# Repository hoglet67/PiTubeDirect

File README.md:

# PiTubeDirect
PiTubeDirect is a low cost Second Processor project for Acorn's 8-bit machines (Beeb, Master, Electron, Atom)
which uses two cheap chips to interface a Raspberry Pi to the Tube connector.

The Pi emulates one of a number of CPUs, and also the Tube interface chip.

A Pi Zero can emulate a 6502 Second Processor running at 274MHz.

For more information, see the project [Wiki](../../wiki).

Here's the minimal configuration, using a Pi Zero and a DIY two-chip level shifter: 

Benchmark results for the 65C02 Second Processor:

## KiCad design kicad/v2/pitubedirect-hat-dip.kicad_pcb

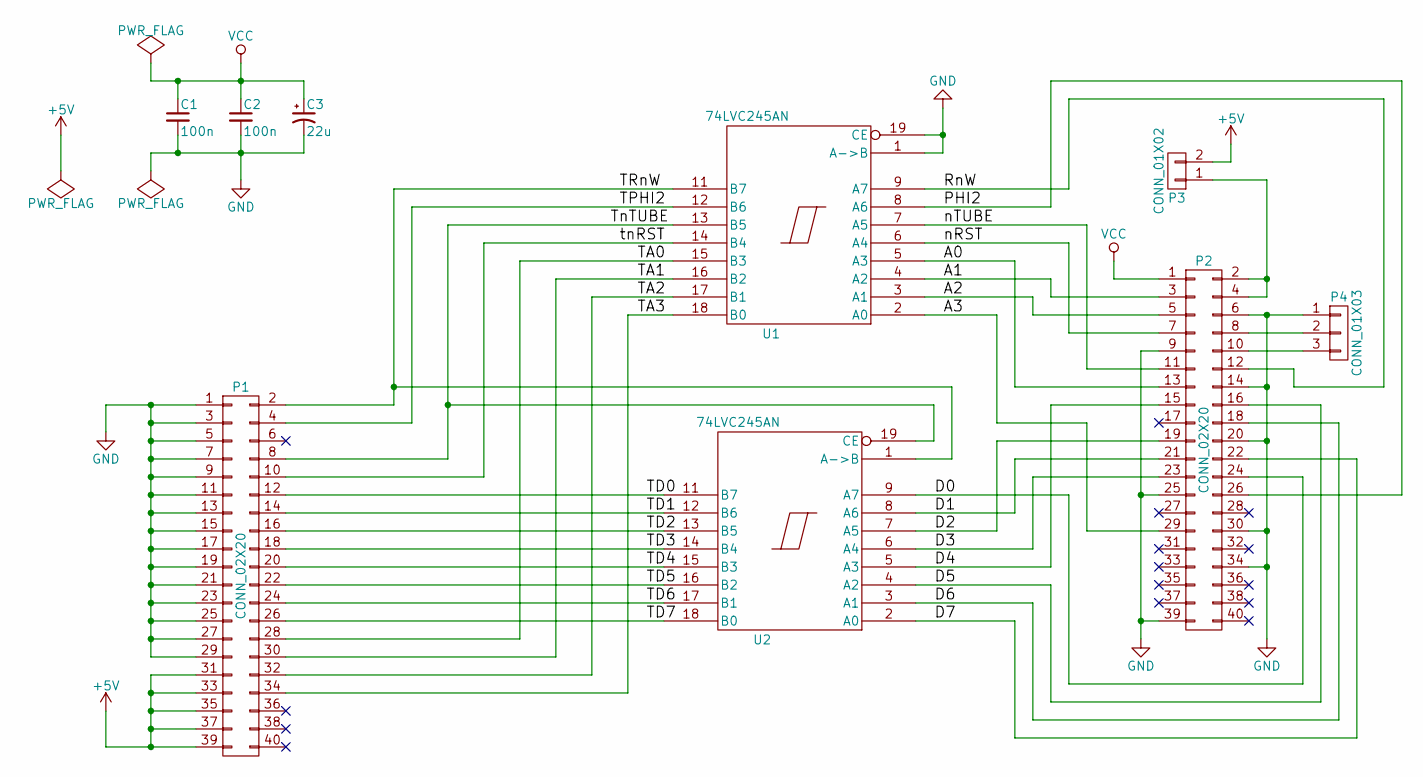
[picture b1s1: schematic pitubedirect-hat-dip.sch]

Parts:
C1, C2: 100n; C_Rect_L7_W2_P5
C3: 22u; C1V8
P1: CONN_02X20; Pin_Header_Straight_2x20
P2: CONN_02X20; Socket_Strip_Straight_2x20
P3: CONN_01X02; Pin_Header_Straight_1x02
P4: CONN_01X03; Pin_Header_Straight_1x03
U1, U2: 74LVC245AN; DIP-20_W7.62mm

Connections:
+5V: P1.31, P1.33, P1.35, P1.37, P1.39, P3.2
/A0: P2.13, U1.5 (A3)
/A1: P2.3, U1.4 (A2)
/A2: P2.5, U1.3 (A1)
/A3: P2.29, U1.2 (A0)
/D0: P2.24, U2.9 (A7)
/D1: P2.21, U2.8 (A6)
/D2: P2.19, U2.7 (A5)
/D3: P2.23, U2.6 (A4)
/D4: P2.15, U2.5 (A3)
/D5: P2.16, U2.4 (A2)
/D6: P2.18, U2.3 (A1)
/D7: P2.22, U2.2 (A0)
/PHI2: P2.26, U1.8 (A6)
/RnW: P2.12, U1.9 (A7)
/TA0: P1.28, U1.15 (B3)
/TA1: P1.30, U1.16 (B2)
/TA2: P1.32, U1.17 (B1)
/TA3: P1.34, U1.18 (B0)
/TD0: P1.12, U2.11 (B7)
/TD1: P1.14, U2.12 (B6)
/TD2: P1.16, U2.13 (B5)
/TD3: P1.18, U2.14 (B4)
/TD4: P1.20, U2.15 (B3)
/TD5: P1.22, U2.16 (B2)
/TD6: P1.24, U2.17 (B1)
/TD7: P1.26, U2.18 (B0)
/TPHI2: P1.4, U1.12 (B6)
/TRnW: P1.2, U1.11 (B7), U2.1 (A->B)
/TnTUBE: P1.8, U1.13 (B5), U2.19 (CE)
/nRST: P2.7, U1.6 (A4)
/nTUBE: P2.11, U1.7 (A5)
/tnRST: P1.10, U1.14 (B4)
GND: C1.2, C2.2, C3.2, P1.1, P1.3, P1.5, P1.7, P1.9, P1.11, P1.13, P1.15, P1.17, P1.19, P1.21, P1.23, P1.25, P1.27, P1.29, P2.6, P2.9, P2.14, P2.20, P2.25, P2.30, P2.34, P2.39, P4.1, U1.1 (A->B), U1.10 (GND), U1.19 (CE), U2.10 (GND)
unnamed: P2.2, P2.4, P3.1
unnamed: P2.8, P4.2
unnamed: P2.10, P4.3
VCC: C1.1, C2.1, C3.1, P2.1, U1.20 (VCC), U2.20 (VCC)

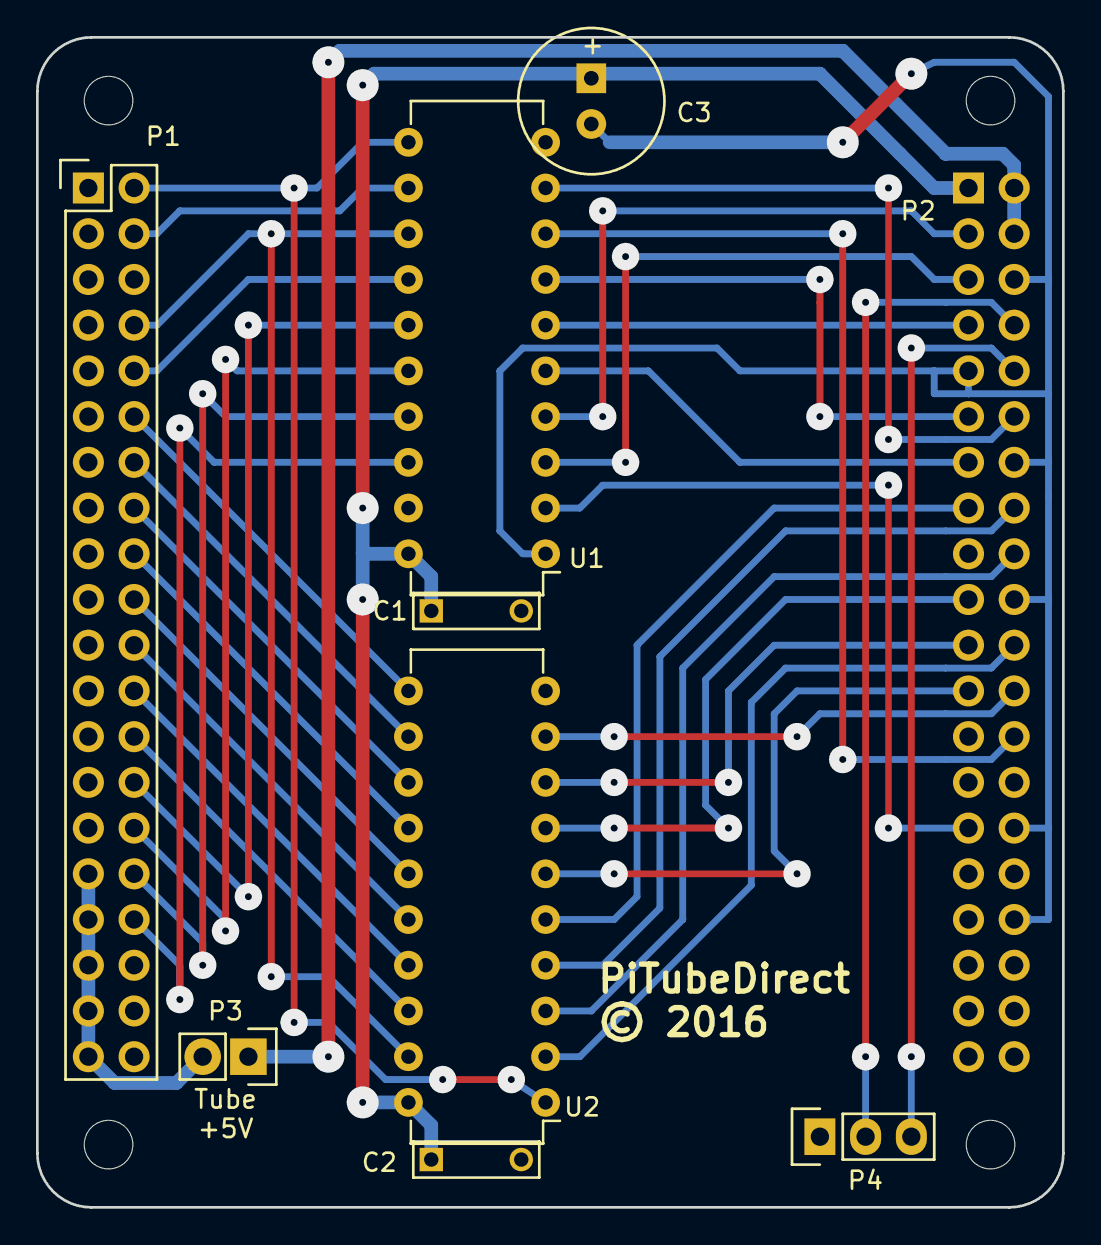
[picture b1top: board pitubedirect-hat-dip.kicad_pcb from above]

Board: 2 copper layers, 57.0 x 65.0 mm, 9 parts (0 on the bottom side), 38 nets.

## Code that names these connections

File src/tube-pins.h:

#include "rpi-base-asm.h"

#define ASS_GPFSEL0 (PERIPHERAL_BASE + 0x200000)  // controls GPIOs 0..9
#define ASS_GPFSEL1 (PERIPHERAL_BASE + 0x200004)  // controls GPIOs 10..19
#define ASS_GPFSEL2 (PERIPHERAL_BASE + 0x200008)  // controls GPIOs 20..29
#define ASS_GPSET0  (PERIPHERAL_BASE + 0x20001C)
#define ASS_GPCLR0  (PERIPHERAL_BASE + 0x200028)
#define ASS_GPLEV0  (PERIPHERAL_BASE + 0x200034)
#define ASS_GPEDS0  (PERIPHERAL_BASE + 0x200040)
#define ASS_FIQCTRL (PERIPHERAL_BASE + 0x00B20C)

//    A2 – Green  - Pin 5  – GPIO1  (GPIO3 on later models)
//    A1 – Blue   - Pin 3  – GPIO0  (GPIO2 on later models)
//    A0 – Purple – Pin 13 – GPIO21 (GPIO27 on later models)
//    D7 – Grey   - Pin 22 – GPIO25
//    D6 – White  - Pin 18 – GPIO24
//    D5 – Black  - Pin 16 – GPIO23
//    D4 – Brown  - Pin 15 – GPIO22
//    D3 – Red    - Pin 23 – GPIO11
//    D2 – Orange – Pin 19 – GPIO10
//    D1 – Yellow – Pin 21 – GPIO9
//    D0 – Green  - Pin 24 – GPIO8
//  nRST – Blue   - Pin 7  – GPIO4
// nTUBE – Purple – Pin 11 – GPIO17
//  nIRQ
//  Phi2 – Grey   - Pin 26 – GPIO7
//   RnW – White  - Pin 12 – GPIO18
//   GND – Black  - Pin 25 – GND

#define D0_BASE      (8)
#define D4_BASE      (22)

#define D7_PIN       (25)     // C2
#define D6_PIN       (24)     // C2
#define D5_PIN       (23)     // C2
#define D4_PIN       (22)     // C2
#define D3_PIN       (11)     // C1
#define D2_PIN       (10)     // C1
#define D1_PIN       (9)      // C0
#define D0_PIN       (8)      // C0

#define MAGIC_C0     ((1 << (D0_PIN * 3)) | (1 << (D1_PIN * 3)))
#define MAGIC_C1     ((1 << ((D2_PIN - 10) * 3)) | (1 << ((D3_PIN - 10) * 3)))
#define MAGIC_C2     ((1 << ((D4_PIN - 20) * 3)) | (1 << ((D5_PIN - 20) * 3)))
#define MAGIC_C3     ((1 << ((D6_PIN - 20) * 3)) | (1 << ((D7_PIN - 20) * 3)))

#define A2_PIN_40PIN       (3)
#define A1_PIN_40PIN       (2)
#define A0_PIN_40PIN       (27)

#define A2_PIN_26PIN       (1)
#define A1_PIN_26PIN       (0)
#define A0_PIN_26PIN       (21)

#define PHI2_PIN     (7)
#define NTUBE_PIN    (17)
#define NRST_PIN     (4)
#define RNW_PIN      (18)

#define D7_MASK      (1 << D7_PIN)
#define D6_MASK      (1 << D6_PIN)
#define D5_MASK      (1 << D5_PIN)
#define D4_MASK      (1 << D4_PIN)
#define D3_MASK      (1 << D3_PIN)
#define D2_MASK      (1 << D2_PIN)
#define D1_MASK      (1 << D1_PIN)
#define D0_MASK      (1 << D0_PIN)

#define PHI2_MASK    (1 << PHI2_PIN)
#define NTUBE_MASK   (1 << NTUBE_PIN)
#define NRST_MASK    (1 << NRST_PIN)
#define RNW_MASK     (1 << RNW_PIN)

#define ATTN_MASK    (1 << ATTN_PIN)
#define OVERRUN_MASK (1 << OVERRUN_PIN)
#define GLITCH_MASK  (1 << GLITCH_PIN)

#define D30_MASK     (D3_MASK | D2_MASK | D1_MASK | D0_MASK)
#define D74_MASK     (D7_MASK | D6_MASK | D5_MASK | D4_MASK)
#define D_MASK       (D74_MASK | D30_MASK)


#define TEST_PIN_26PIN     (27)
#define TEST_PIN_40PIN     (21)

#define TEST_PIN     (21)
#define TEST_MASK    (1 << TEST_PIN)
#define TEST2_PIN    (20)
#define TEST2_MASK   (1 << TEST2_PIN)
#define TEST3_PIN    (16)
#define TEST3_MASK   (1 << TEST3_PIN)

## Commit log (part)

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2022-06-02 Add consts
2022-06-03 Updated the release name to Hognose-rc5
2022-06-04 Jit make better use of strd
2022-06-05 Frame Buffer: VDU 23,0,10/11 controls cursor start/end row
2022-06-05 Jit.s : very simple optimiser to remove duplicate flag settings
    Very simple optimiser such that if the next instruction also sets the NZ flags then the current instruction doesn't need to set the flags. This can help to remove pipeline stalls especially after a l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
2022-06-05 jit.s : remove optimisation at appears to slow ARMv6 systems
2022-06-06 Frame Buffer: implement OSBYTE &A0 X=&4F/&60/&61
2022-06-06 no need to fill in last words of branches now
2022-06-06 Jit.s speed up Store ZP generation
2022-06-08 Updated the release name to Hognose-rc6
2022-06-09 PDP-11 Co Pro - fix an infinite logging loop on odd address traps
2022-06-19 Arm dissassembler : fix instructiosn of the form LDR rd,[rn,rm,LSL #xx]!
    Also remove addr_mask
2022-06-19 Arm diss : remove addr_mask
2022-06-21 arm-start.S : speed up initialisation
2022-06-25 llib6502 disassembler: significantly speed up code
    this is required so the the jitter live tracking will work on a Pizero
2022-06-25 UART : increase tx buffer size to 4Mbytes
2022-06-25 jit : large changes
    IRQ handler now local instead of using the global one
    flags used to hold of FAKE irqs till safe points in the code
    Issue #125 : memory leak removed
    various tiding
    Pizero : better instruction cache flush to improve live tracing performance also removes glitch in twinhead
    whitespace improvements
2022-06-25 Jit : remove useless ifdef
2022-07-17 ROL and ASL $80 + optimise lda #0 , JMP($0000,X)
2022-07-17 LDA $0000,Y optimise + tidy
2022-07-17 fix typo in jmp ($0000,x)
2022-07-18 faster JSR
2022-07-20 Optimise logical $0000,X or Y
2022-07-21 for dual issue remove flag setting instructions
2022-07-21 pipeline adjustment
2022-07-21 remove duplicate code
2022-07-23 CLC /SEC add to flag optimisation
2022-07-23 reorder ldy $00 ldx $00
2022-07-23 forward flags looking optimiser
2022-07-24 Add prefetch Instruction cacheline + tidy
2022-07-25 nops are faster than branches on ARMv8
2022-07-26 Tidy up registers around irqs nmis, free up R2 to be used by RTSR2
    492MHz
2022-07-29 faster sta
    528MHz. bias sta zp to non self modifying code
2022-08-16 PDP-11 Co Pro - updated client rom to 0.30 (just a version number change from 0.28e)
2022-10-07 remove cppcheck warnings
2023-01-24 Tube ULA: Added tube_debug support
2023-01-24 Tube ULA: Fix #ifdef typo
2023-01-28 gcc appears not to support eret for armv7
2023-01-28 fix cppcheck warning
2023-01-28 split out font_t and font_catalog to remove warnings
2023-01-28 Update ClockSP to ClockSP5 ( 5.08)
2023-01-28 remove warnings and simplify code
2023-01-28 Tidy
2023-01-28 Cppcheck script
2023-01-29 Add const keyword
2023-01-29 Fix binutiles 2.39 linker warning and simplify
2023-01-29 shrink pandora rom ( truncate x00)
2023-01-31 Remove unnecessary init_info() function as we nolonger take over the main VPU
2023-02-03 reduce cpu time copying strings around and reallocing ram
2023-02-04 use calloc
2023-02-05 Move IRQ handler out of AUX UART code
2023-02-05 use strcasestr
2023-03-18 Updated the release name to Hognose-fixes
2023-04-28 Add a pullup to nTube (see BeebFPGA issue 25)
2023-05-22 Fix potential buffer overrun
2023-06-09 Framebuffer: Fix memory init issues that cause a crash on startup
2023-06-10 Native ARM Co Pro: *PIVDU 2 OSWRCH Redirector copied from wrong address (#170)
2023-06-11 tube-commands : define flags variable
2023-06-11 swi : Rework swi calls so that the compiler knows what is going on
    This has the effect some of the directives can be removed and the optimiser can produce much better code.
2023-06-11 Tube-commands fix missing bracket from last commit
2023-06-12 arm-start.S : move functions into rpi-asm-helpers.c this helps the optimiser
    Also remove unused startup.h includes
2023-06-15 tube-commands : fix sscanf types in *FX command
2023-06-15 copro-65tubeasm.S : move add local irq handler
2023-06-16 tube-ula.c : remove unused functions and tidy NMI ack IRQ
2023-06-16 tube-lib.c : simplify restoring of IRQs
2023-06-16 Copro-65tubeasm : Stop disbling IRQs when doing ioacesses
2023-06-18 jit.S fix bug where call&300 and *fx14,4 would be slow
2023-06-18 Fix command line debug uart baud rate
2023-06-18 tube-lib.c : force enabling IRQs in tube write not just restore them
2023-06-18 rpi-asm-helpers.c : add enable/disable FIQ
2023-06-18 tube-ula.c : change to just disabling and enabling FIQs directly
2023-06-19 tube-ula : FIQs / INTs restore previous status.
    I can't find an issues with the previous method ,but I think I'm happier with a complete restore of the FIQ /IRQ status
2023-06-19 CMakelist.txt : revert earlier commit as some of the flags are gcc13.1 only
2023-06-21 Framebuffer: User defined characters persist across mode changes (#171)
2023-06-21 6502: CALL &2000 should output *FX 147 in elk mode (#160)
2023-06-25 Jit.s : fix for #125 BRK in IRQ leaks memory,
2023-07-09 Fast 6502, Lib 6502 - fix JSR with the last byte overlapping the stack pointer
2023-07-22 Jit.S : Fix JSR /RTS/RTI stack wrapping bug
2023-07-24 tubevc.s : typo
2023-07-28 tube_swi.c : Fix gcc pedant warnings #108
2023-07-29 CMakeLists : remove left over LTO files
2023-07-29 jit.S : fix stack wrapping for RTI and INTR
2023-07-31 jit.S : Fixeds JSR /RTS stack wrapping issue
2023-07-31 jit.S : Tidy RTS RTS PHP
2023-07-31 jit.S : correct RTI
2023-08-01 jit.S : remove duplicated code
2023-08-01 jit.S : speedup iostores
2023-08-02 jit.S : faster STA $00 if there isn't self modifying code in ZP
2023-08-13 Native ARM Co Pro: Fix *ARMBASIC crash (introduced in c0d15e0)
2023-08-13 info.c: Simplify get_cmdline_prop
2023-08-18 copro-65tubeasm.S : Fix brk overflowing
2023-08-18 Co Pro RISC-V: Local command processor and *HELP/*GO commands
2023-08-18 Co Pro RISC-V: Debugger: correct memory width to 8 bits
2023-08-18 Co Pro RISC-V: Comments only
2023-08-18 Co Pro RISC-V: Make memory accessor data type uint32_t
2023-08-18 Co Pro RISC-V: Initial checkin of files
2023-08-18 Co Pro RISC-V: Disassembler: Simplify branch formatting when rs2=zero
2023-08-18 Co Pro RISC-V: Start work on ECall Handler
2023-08-18 Co Pro RISC-V: rework error handler
2023-08-18 Co Pro RISC-V: Tuberom bugfix
2023-08-18 Co Pro RISC-V: Debugger improvements
2023-08-18 Co Pro RISC-V: Fix a bug that prevented debugging of tube reads
2023-08-18 Co Pro RISC-V: Disassembler: add MRET
2023-08-18 Co Pro RISC-V: Continue work on ECall Handler
2023-08-18 Co Pro RISC-V: *TEST calculates Pi in C
2023-08-18 Co Pro RISC-V: OSWORD, *TEST, hex/dec output
2023-08-18 Co Pro RISC-V: Tube ROM: IRQ partly done
2023-08-18 Co Pro RISC-V: Add HelloWorld Tube ROM
2023-08-18 Co Pro RISC-V: Implement prep_env and enter_code
2023-08-18 Co Pro RISC-V: Lots of file system API fixes
2023-08-18 Co Pro RISC-V: Implement OS_BPUT, OS_ARGS, OS_GBPB (all untested)
2023-08-18 Co Pro RISC-V: Maintain 16-byte stack alignment
2023-08-18 Co Pro RISC-V: Fix whitespace
2023-08-18 Co Pro RISC-V: Fix minor register name typo in debugger
2023-08-18 Co Pro RISC-V: Implement OS_FILE
2023-08-18 Comments only (API documentation)
2023-08-18 Co Pro RISC-V: Tube ROM now at FC0000
2023-08-20 Co Pro RISC-V: codespell fixes
2023-08-20 Co Pro RISC-V: cppcheck fixes (part 2)
2023-08-22 jit.S : Fix for self modifiying code in ZP
2023-08-22 Jit.S : clear flags just incase they aren't zero
2023-09-02 UART : Reduce CPU load
    Round BAUD rate correctly helps at >3Mbaud
    Reduce CPU load when writing bytes to the UART
    Add flush flush function so that Exception handlers can Empty the UART before adding more characters to the UART
    Dump functions can write to the UART buffer and then be flushed
2023-09-02 Jit : Add a bit of support for the debugger and tidy
2023-09-02 jit_debug.c : increase spacing so bbr7 zp,pcxx fits
2023-09-03 jit.s : optimise IO store
2023-09-03 darm : FIX mrs decode
2023-09-04 jit.s typo and speed up stz
2023-09-04 Fix cppcheck warnings
2023-09-06 Tube ULA: Fix two byte data transfer flags incorrect (#179)
2023-09-08 Co Pro RISC-V: Update OSFILE and OSGBPB APIs to use individual registers (#180, #181)
2023-09-08 Co Pro RISC-V: Update ECALL_BASE to 0x00AC0000 (#183)
2023-09-08 Co Pro RISC-V: Implement Uncaught Exception Handler (#184)
2023-09-09 Co Pro RISC-V: Implement Current Program and OS_SYSCTRL a0=1 (#182)
2023-09-09 Co Pro RISC-V: Use stack for tmp buffers in OSARGS and *PI
2023-09-09 Co Pro RISC-V: *HELP shows correct version
2023-09-09 Co Pro RISC-V: Default uncaught exception handler dumps all registers (#186)
2023-09-09 Co Pro RISC-V: Cosmetic
2023-09-10 Frame Buffer: POINT's offscreen check is not right (#175)
2023-09-11 Co Pro RISC-V: Change error number from 8-bits to 32-bits (#188)
2023-09-11 Co Pro RISC-V: Improve formatting of default uncaught exception handler
2023-09-13 Debugger: Refactor param parsing slightly
2023-09-15 Whitespace only
2023-09-15 Co Pro RISC-V: Improve disassembler (MUL extension, tighten illegal opcodes) (#195)
2023-09-15 Co Pro RISC-V: Improve disassembler (CSR and number base) (#195)
2023-09-19 Co Pro RISC-V: Fix CSR immediate disassembly bug
2023-09-20 Co Pro RISC-V: Clear mie on reset
2023-09-20 Co Pro RISC-V: Make timermatch registers readable
2023-09-20 Co Pro RISC-V: Re-enable interrupts when calling error handler
2023-09-24 Updated the release name to Indigo-alpha3
2023-09-26 RISC-V Co Processor: Make R4 IRQ Re-enterant (#199)
2023-09-26 RISC-V Co Processor: Preserve A7 in local OSCLI commands
2023-10-08 Framebuffer.c : fix cppcheck warnings
2023-10-13 Updated the release name to Indigo-alpha4
2023-10-18 Native ARM: Fix This is not a language causing hard crash on Ctrl-BREAK (#205)
2024-02-29 copro-65tubeasm.S : make 64bit stack alignment clearer
2024-03-02 Should fix bug introduced in last commit and refactor
2024-03-03 whitespace change
2024-03-31 Framebuffer : Fix typos
2024-04-03 Fix Typos
2024-04-30 Any size PDP11 Client ROM loaded to top of memory
2024-04-30 PDP11: Updated PDP client ROM to Tube11v030c-20240429
2024-05-10 Updated the release name to Indigo-alpha7
2024-05-13 Native ARM Co Pro: Implement X SWI Bit (not reentrant) #210
2024-05-26 Fix for certain Pi 1 Models (#211)
2024-07-21 jits.S : Fix DEC <abs> on self modifying code
2024-08-26 copro-armnative.c : correct sprintf type ( found with PVS studio)
2024-08-26 primitives.c : copy and paste error ( found by PVS studio)
2024-08-26 screen_modes.c : bracket left side of ? ( warning from PVS studio)
2024-08-26 debugger.c : put brackets around parameters ( as suggested by PVS sutdio_
2024-08-26 rpi-mailbox-interface.c : tidy up types
2024-11-13 80x86 Co Pro: Throw an illegal instruction interrupt on opcode 0xFF 0xFF
2024-12-13 Fast 6502 Co Pro: Allow STZ absolute to write to tube registers
2024-12-14 Fast 6502 Co Pro: reset banksel page mappings on every reset
2024-12-20 Fix compilation of 65816.c
    Fix the following issue:
    In file included from PiTubeDirect/src/65816/65816.c:8:
    PiTubeDirect/src/65816/65816.h:23:1: error: unknown type name 'uint8_t'
    23 | uint8_t *w65816_init(void *rom, uint32_t nativeVectBank);
    | ^~~~~~~
    PiTubeDirect/src/65816/65816.h:1:1: note: 'uint8_t' is defined in header '<stdint.h>'; did you forget to '#include <stdint.h>'?
2025-07-14 32016: fix a regression in 89a91505 (17/07/2021) that broke the clock demo
2025-10-07 KiCAD: Added PDF schematic
2026-02-28 Updated the release name to Indigo-alpha10
2026-03-26 Frame Buffer: Add support for double buffering (via OSBYTE &70/&71) (fixes #166)
2026-03-27 Frame Buffer: Calculare max number of screen buffers dynamically using 2160 / height
2026-03-27 Frame Buffer: implement default banks in OSBYTE 112,113
2026-03-30 Frame Buffer: Teletext STEADY is set-at not set-after
2026-04-05 Frame Buffer: Switch VDU 23,8 calculation to using window-relative coords so clipping matches MOS 3.20
2026-04-05 Frame Buffer: Initial implementation of VDU 23,8 (Clear Block)
2026-04-05 Frame Buffer: New fill segment now workimg
2026-04-06 Frame Buffer: Initial implementation of VDU 23,7 (Scroll Rectangle)
2026-04-09 Frame Buffer: Use int rather than int32_t for consistency
2026-04-09 Frame Buffer: Improve filled segment end point calculation
2026-04-09 Frame Buffer: Fix bug in previous commit

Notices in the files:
kicad/v2/pitubedirect-hat-dip.kicad_pcb:
© 2016
